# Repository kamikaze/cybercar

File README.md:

# CyberCar
This project is for my Audi A6 (C5) 2004. But I'm trying to make it compatible with as many different cars as possible.
Some of ideas:

1. Connect to CAN bus and read/write to it.

2. Useful information and/or beautification animation output to one or many displays (OLED?)

3. GPS tracking

4. Connection to internet via WiFi and mobile connection.

5. Multimedia sub-project (as for now - RPi + Pioneer AVH-X7500BT via AV cable)

6. Head/Tail light turn on/off, mode switch (if any) (use RGB led stripes?)

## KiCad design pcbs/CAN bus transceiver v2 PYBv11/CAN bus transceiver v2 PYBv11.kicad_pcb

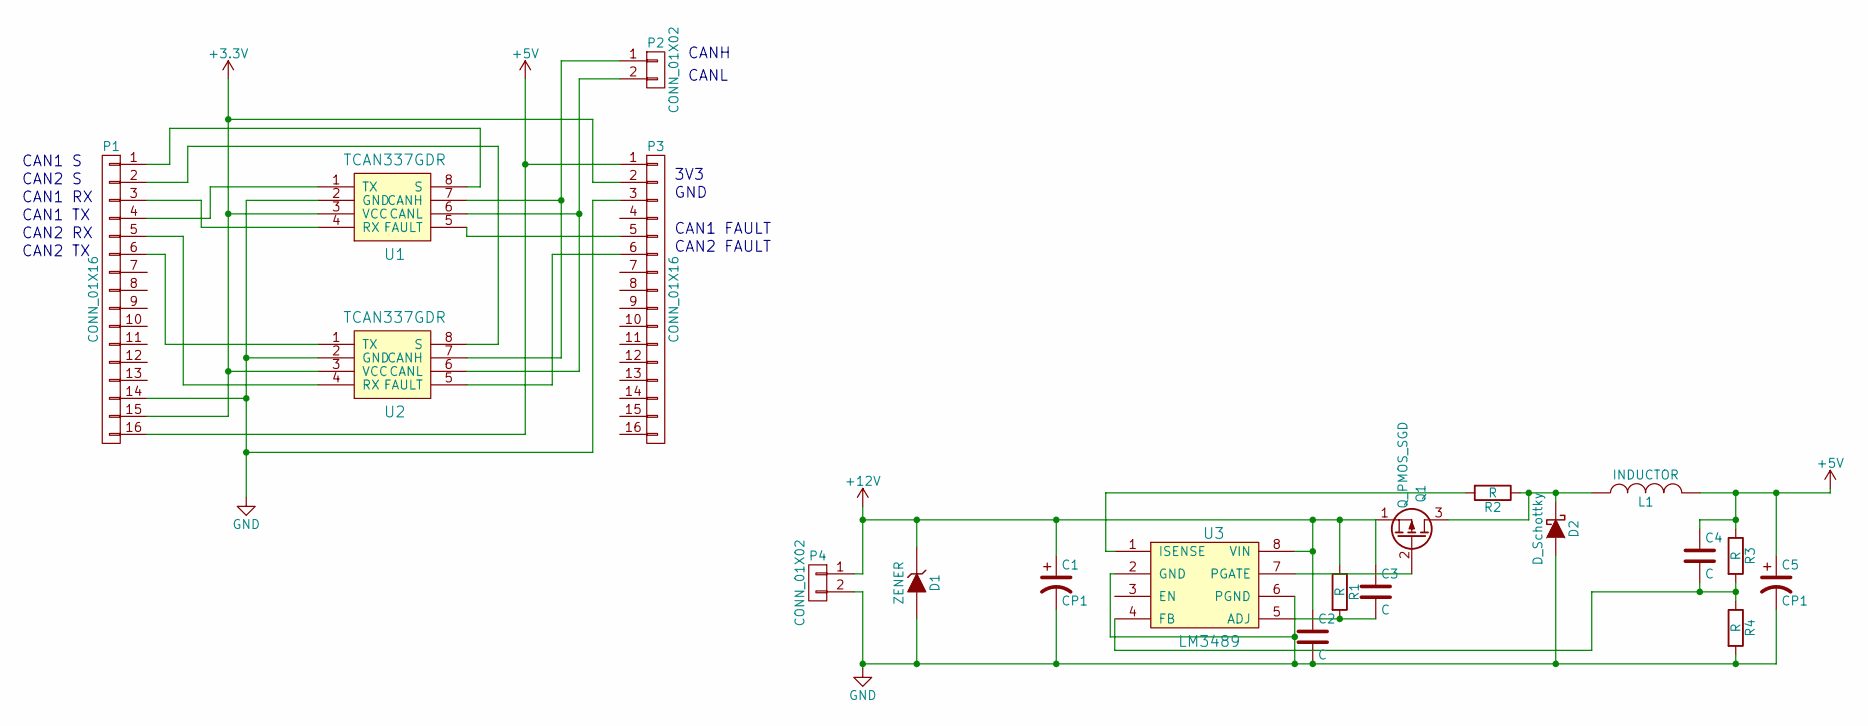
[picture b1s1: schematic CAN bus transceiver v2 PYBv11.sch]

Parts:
C1, C5: CP1; C_Radial_D8_L11.5_P3.5
C2, C3, C4: C; C_0805
D1: ZENER; SOD-523
D2: D_Schottky; Diode_DO-35_SOD27_Horizontal_RM10
L1: INDUCTOR; Inductor_Taiyo-Yuden_NR-80xx_HandSoldering
P1, P3: CONN_01X16; Pin_Header_Straight_1x16
P2, P4: CONN_01X02; JST_XH_S02B-XH-A_02x2.50mm_Angled
Q1: Q_PMOS_SGD; SOT126_SOT32_Housing_Vertical
R1, R2, R3, R4: R; R_0805
U1, U2: TCAN337GDR; SOIC-8_3.9x4.9mm_Pitch1.27mm
U3: LM3489; TSSOP-8_4.4x3mm_Pitch0.65mm

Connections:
+3V3: P1.15, P3.2, U1.3 (VCC), U2.3 (VCC)
+5V: C4.1, C5.1, L1.2, P1.16, P3.1, R3.1
+12V: C1.1, C2.1, C3.1, D1.1 (K), P4.1, Q1.1 (S), R1.1, U3.8 (VIN)
GND: C1.2, C2.2, C5.2, D1.2 (A), D2.2 (A), P1.14, P3.3, P4.2, R4.2, U1.2 (GND), U2.2 (GND), U3.2 (GND), U3.6 (PGND)
unnamed: C3.2, R1.2, U3.5 (ADJ)
unnamed: C4.2, R3.2, R4.1, U3.4 (FB)
unnamed: D2.1 (K), L1.1, Q1.3 (D), R2.1
unnamed: P1.1, U1.8 (S)
unnamed: P1.2, U2.8 (S)
unnamed: P1.3, U1.4 (RX)
unnamed: P1.4, U1.1 (TX)
unnamed: P1.5, U2.4 (RX)
unnamed: P1.6, U2.1 (TX)
unnamed: P2.1, U1.7 (CANH), U2.7 (CANH)
unnamed: P2.2, U1.6 (CANL), U2.6 (CANL)
unnamed: P3.5, U1.5 (FAULT)
unnamed: P3.6, U2.5 (FAULT)
unnamed: Q1.2 (G), U3.7 (PGATE)
unnamed: R2.2, U3.1 (ISENSE)

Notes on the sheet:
CAN1 RX
CAN1 TX
CAN2 RX
CAN2 TX
3V3
GND
CANH
CANL
CAN1 FAULT
CAN2 FAULT
CAN2 S
CAN1 S

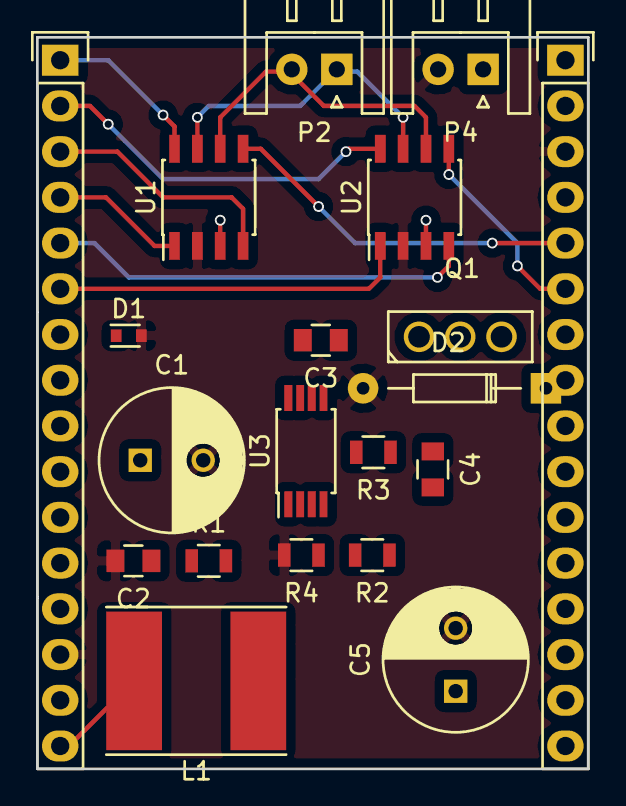
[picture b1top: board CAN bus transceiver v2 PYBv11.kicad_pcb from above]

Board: 2 copper layers, 30.6 x 40.6 mm, 20 parts (0 on the bottom side), 19 nets.

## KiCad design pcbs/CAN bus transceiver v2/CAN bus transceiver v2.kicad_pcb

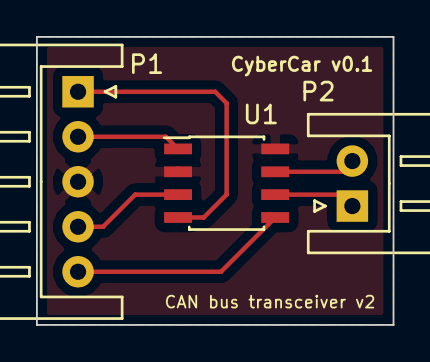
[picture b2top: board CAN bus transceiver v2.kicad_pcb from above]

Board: 2 copper layers, 19.8 x 16.0 mm, 3 parts (0 on the bottom side), 7 nets.

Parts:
P1: CONN_01X05; JST_XH_S05B-XH-A_05x2.50mm_Angled
P2: CONN_01X02; JST_XH_S02B-XH-A_02x2.50mm_Angled
U1: TCAN337GDR; SOIC-8_3.9x4.9mm_Pitch1.27mm

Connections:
+3V3: P1.4, U1.3
GND: P1.3, U1.2, U1.8
unnamed: P1.1, U1.4
unnamed: P1.2, U1.1
unnamed: P1.5, U1.5
unnamed: P2.1, U1.6
unnamed: P2.2, U1.7

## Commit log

2016-10-12 added CAN bus transceiver
2016-10-28 working on CAN bus transceiver v2 PYBv11 shield
2016-11-08 doc: added docs for Pioneer AVH-X7500BT and Texas Instruments LM3489
2016-11-18 can: added components for LM3489 wiring
2016-11-20 can: placing LM3489 components on board
2016-11-30 can: changed Zenner diode footprint
2016-12-27 imu: added datasheets for L3GD20 and LSM303DLHC
2016-12-27 readme: update
2019-06-06 moved transceiver shield for PyBoard v1.1 to an external repo, added TCAN33x datasheet
